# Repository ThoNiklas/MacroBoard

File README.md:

First version of a macro board with 16 keys, 2 rotary encoders and 4 LEDs.

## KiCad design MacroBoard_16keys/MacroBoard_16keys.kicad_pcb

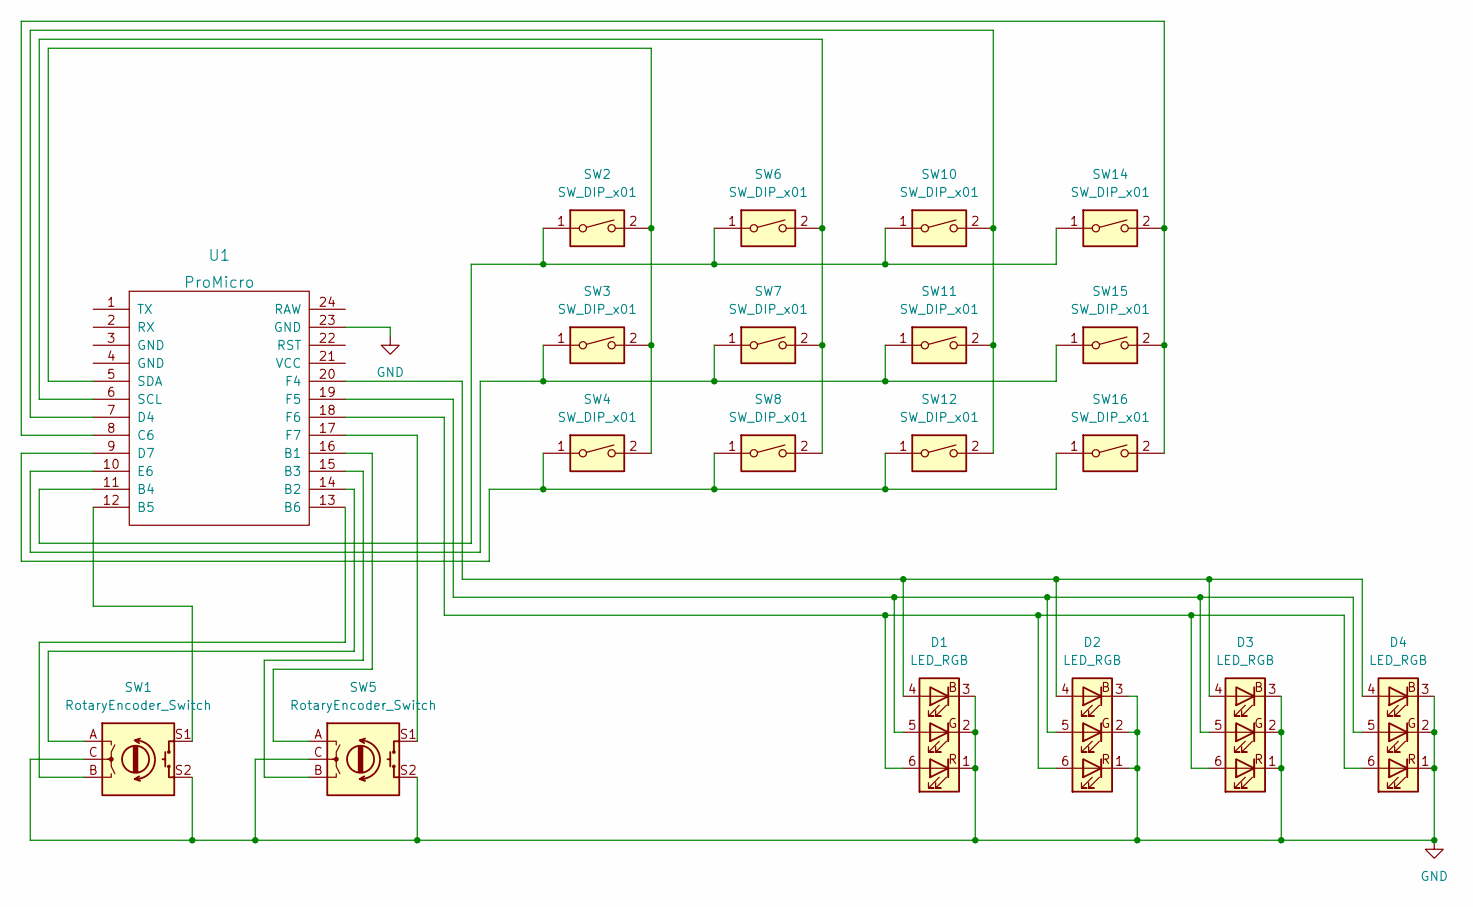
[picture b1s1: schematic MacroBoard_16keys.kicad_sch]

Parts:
D1, D2, D3, D4: LED_RGB; LED_RGB_5050-6
SW1, SW5: RotaryEncoder_Switch; RotaryEncoder_Alps_EC11E-Switch_Vertical_H20mm
SW2, SW3, SW4, SW6, SW7, SW8, SW10, SW11, SW12, SW14, SW15, SW16: SW_DIP_x01; SW_Cherry_MX_1.00u_PCB
U1: ProMicro

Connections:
GND: D1.1 (RK), D1.2 (GK), D1.3 (BK), D2.1 (RK), D2.2 (GK), D2.3 (BK), D3.1 (RK), D3.2 (GK), D3.3 (BK), D4.1 (RK), D4.2 (GK), D4.3 (BK), SW1.C, SW1.S2, SW5.C, SW5.S2, U1.23 (GND)
unnamed: D1.4 (BA), D2.4 (BA), D3.4 (BA), D4.4 (BA), U1.20 (F4)
unnamed: D1.5 (GA), D2.5 (GA), D3.5 (GA), D4.5 (GA), U1.19 (F5)
unnamed: D1.6 (RA), D2.6 (RA), D3.6 (RA), D4.6 (RA), U1.18 (F6)
unnamed: SW1.A, U1.14 (B2)
unnamed: SW1.B, U1.13 (B6)
unnamed: SW1.S1, U1.12 (B5)
unnamed: SW2.2, SW3.2, SW4.2, U1.5 (SDA)
unnamed: SW5.A, U1.16 (B1)
unnamed: SW5.B, U1.15 (B3)
unnamed: SW5.S1, U1.17 (F7)
unnamed: SW6.2, SW7.2, SW8.2, U1.6 (SCL)
unnamed: SW2.1, SW6.1, SW10.1, SW14.1, U1.11 (B4)
unnamed: SW10.2, SW11.2, SW12.2, U1.7 (D4)
unnamed: SW3.1, SW7.1, SW11.1, SW15.1, U1.10 (E6)
unnamed: SW4.1, SW8.1, SW12.1, SW16.1, U1.9 (D7)
unnamed: SW14.2, SW15.2, SW16.2, U1.8 (C6)

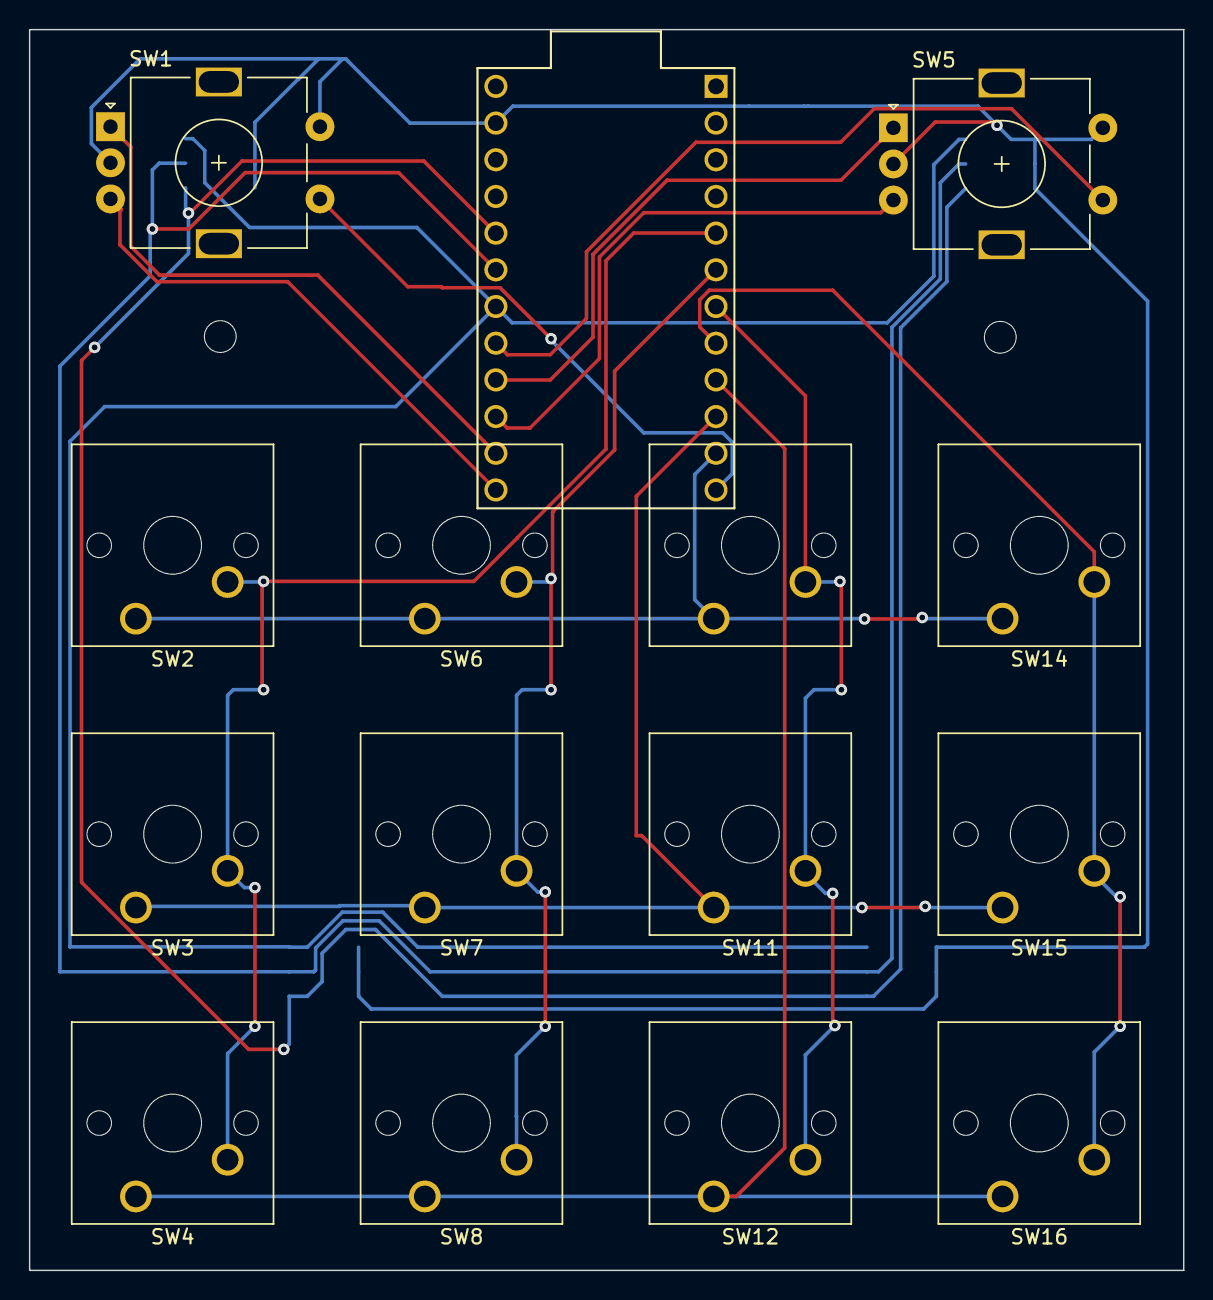
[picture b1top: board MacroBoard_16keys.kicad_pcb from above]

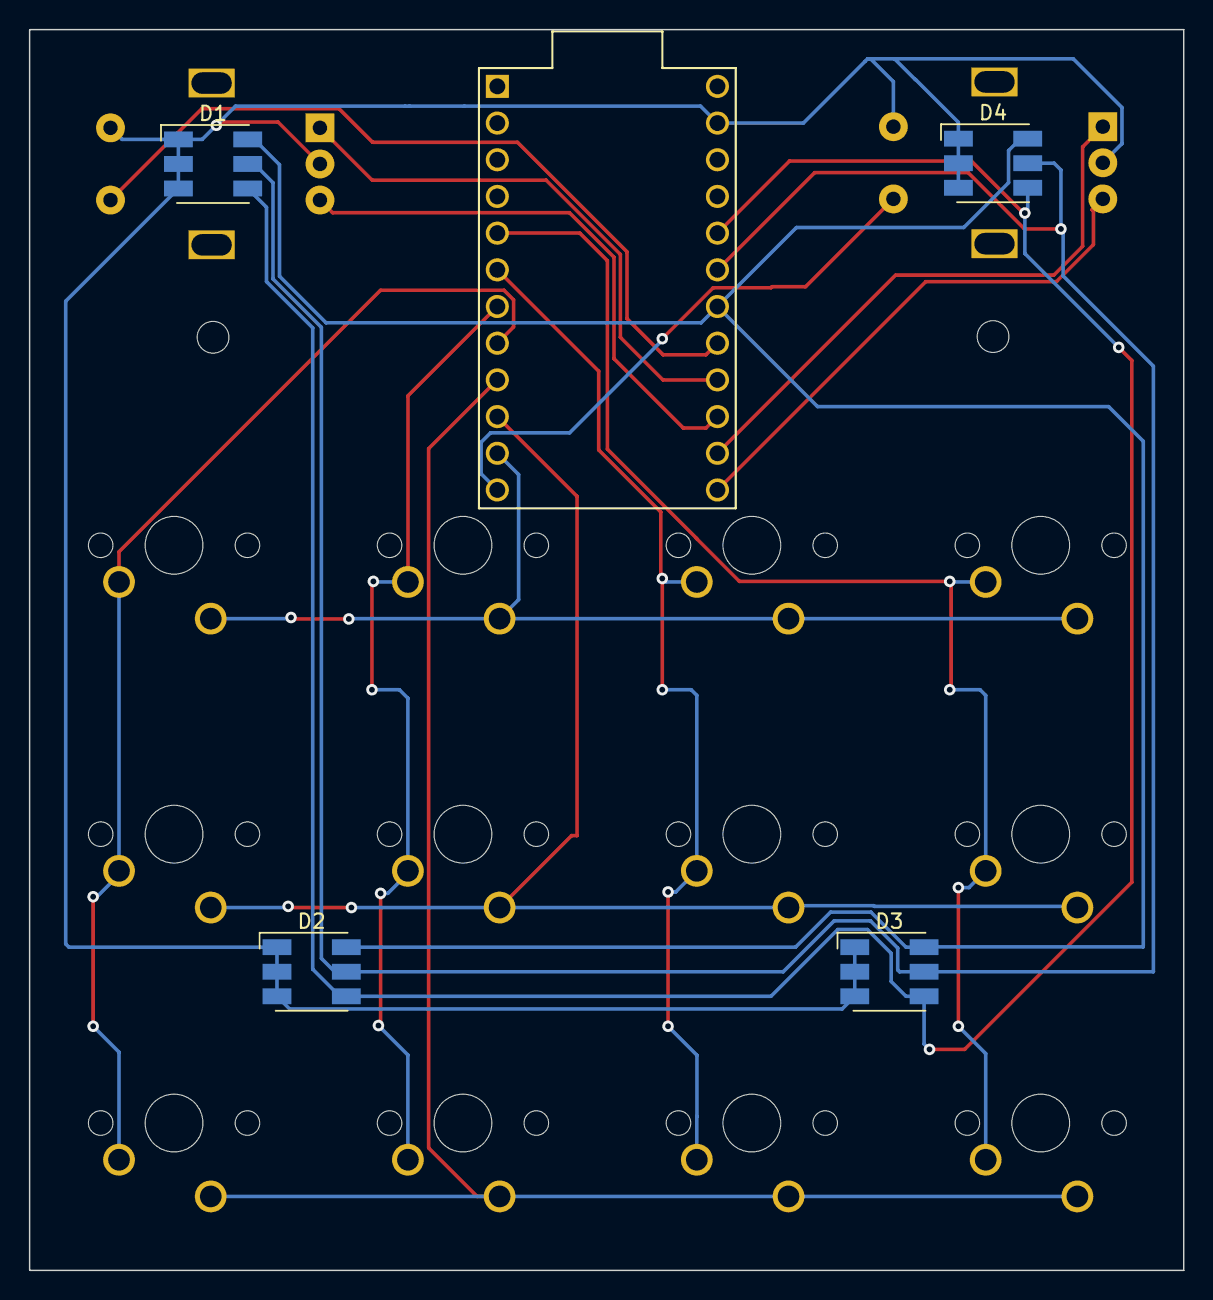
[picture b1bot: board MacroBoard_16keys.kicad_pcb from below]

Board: 2 copper layers, 79.9 x 85.9 mm, 19 parts (5 on the bottom side), 17 nets.

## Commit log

2023-03-05 Initial commit Added KiCad-file Added the keys and the LEDs (not final footprint)
2023-03-05 Now added Kicad-file
2023-03-17 Added 3D-model Added Gerber files Added code
2023-03-17 Changed the boring hole in the top to 1,8
2023-03-27 Added mode switching with changing LED colors
2023-03-27 Fixed LED on/off toggle
2023-03-28 No shortcut with 0 new top.stl
2023-03-28 new top with higher rim
